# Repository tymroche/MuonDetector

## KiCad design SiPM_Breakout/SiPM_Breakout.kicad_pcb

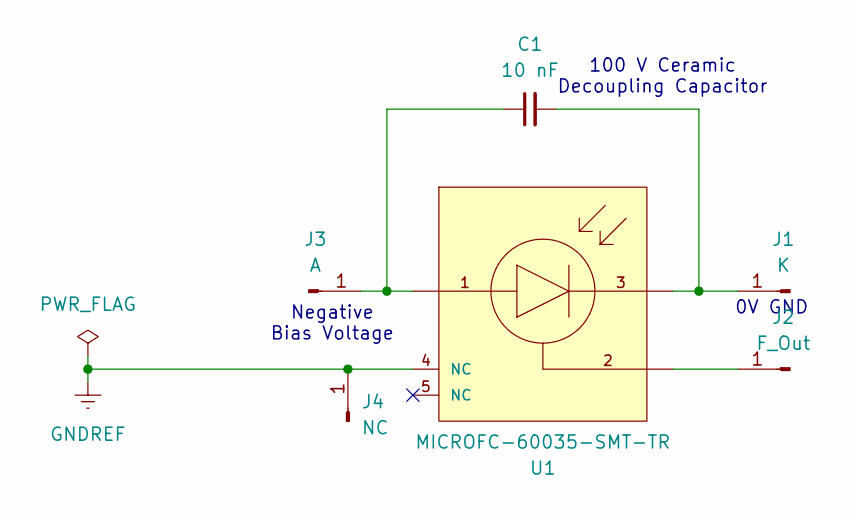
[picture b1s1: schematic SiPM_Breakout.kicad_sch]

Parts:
C1: 10 nF; C_0805_2012Metric_Pad1.18x1.45mm_HandSolder
J1: K; PinHeader_1x01_P1.00mm_Vertical
J2: F_Out; PinHeader_1x01_P1.00mm_Vertical
J3: A; PinHeader_1x01_P1.00mm_Vertical
J4: NC; PinHeader_1x01_P1.00mm_Vertical
U1: MICROFC-60035-SMT-TR; ON_Semiconductor-512AG-07_2018-O-MFG; mouser part number 863-MFC60035SMTTR; digikey description SENSOR PHOTODIODE 420NM 4SMD

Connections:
GNDREF: J4.1 (Pin_1_1), U1.4 (NC)
unnamed: C1.2, J1.1 (Pin_1_1), U1.3 (Cathode)
unnamed: J2.1 (Pin_1_1), U1.2 (Fast_Output)
unnamed: C1.1, J3.1 (Pin_1_1), U1.1 (Anode)

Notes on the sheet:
Negative Bias Voltage
0V GND
100 V Ceramic Decoupling Capacitor

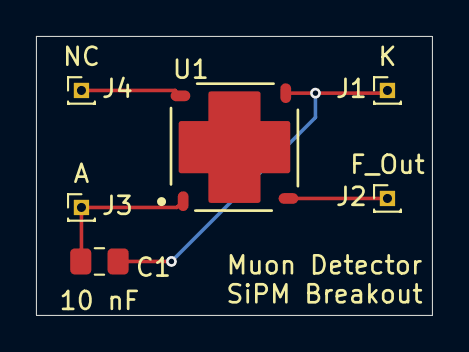
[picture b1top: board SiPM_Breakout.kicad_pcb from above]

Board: 2 copper layers, 22.0 x 15.5 mm, 6 parts (0 on the bottom side), 4 nets.

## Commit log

2026-04-10 Added SiPM Symbol & Footprint
2026-04-10 Added SiPM Documents
2026-04-10 Annotated AND9770 Doc.
2026-04-10 More Annotations
2026-04-11 Finished Annotations + Completed PCB
